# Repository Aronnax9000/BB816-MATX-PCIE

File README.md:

# BB816-PCIe
Adapt Adrien Kohlbecker's BB816 Breakout Board to PCIExpress x16 style connector.

Four slots for expansion cards based on PCIe geometry and the mATX Specification. A 20 pin ATX power supply connector is provided. The board is made to the same specifications as Adrien Kohlbecker's BB816

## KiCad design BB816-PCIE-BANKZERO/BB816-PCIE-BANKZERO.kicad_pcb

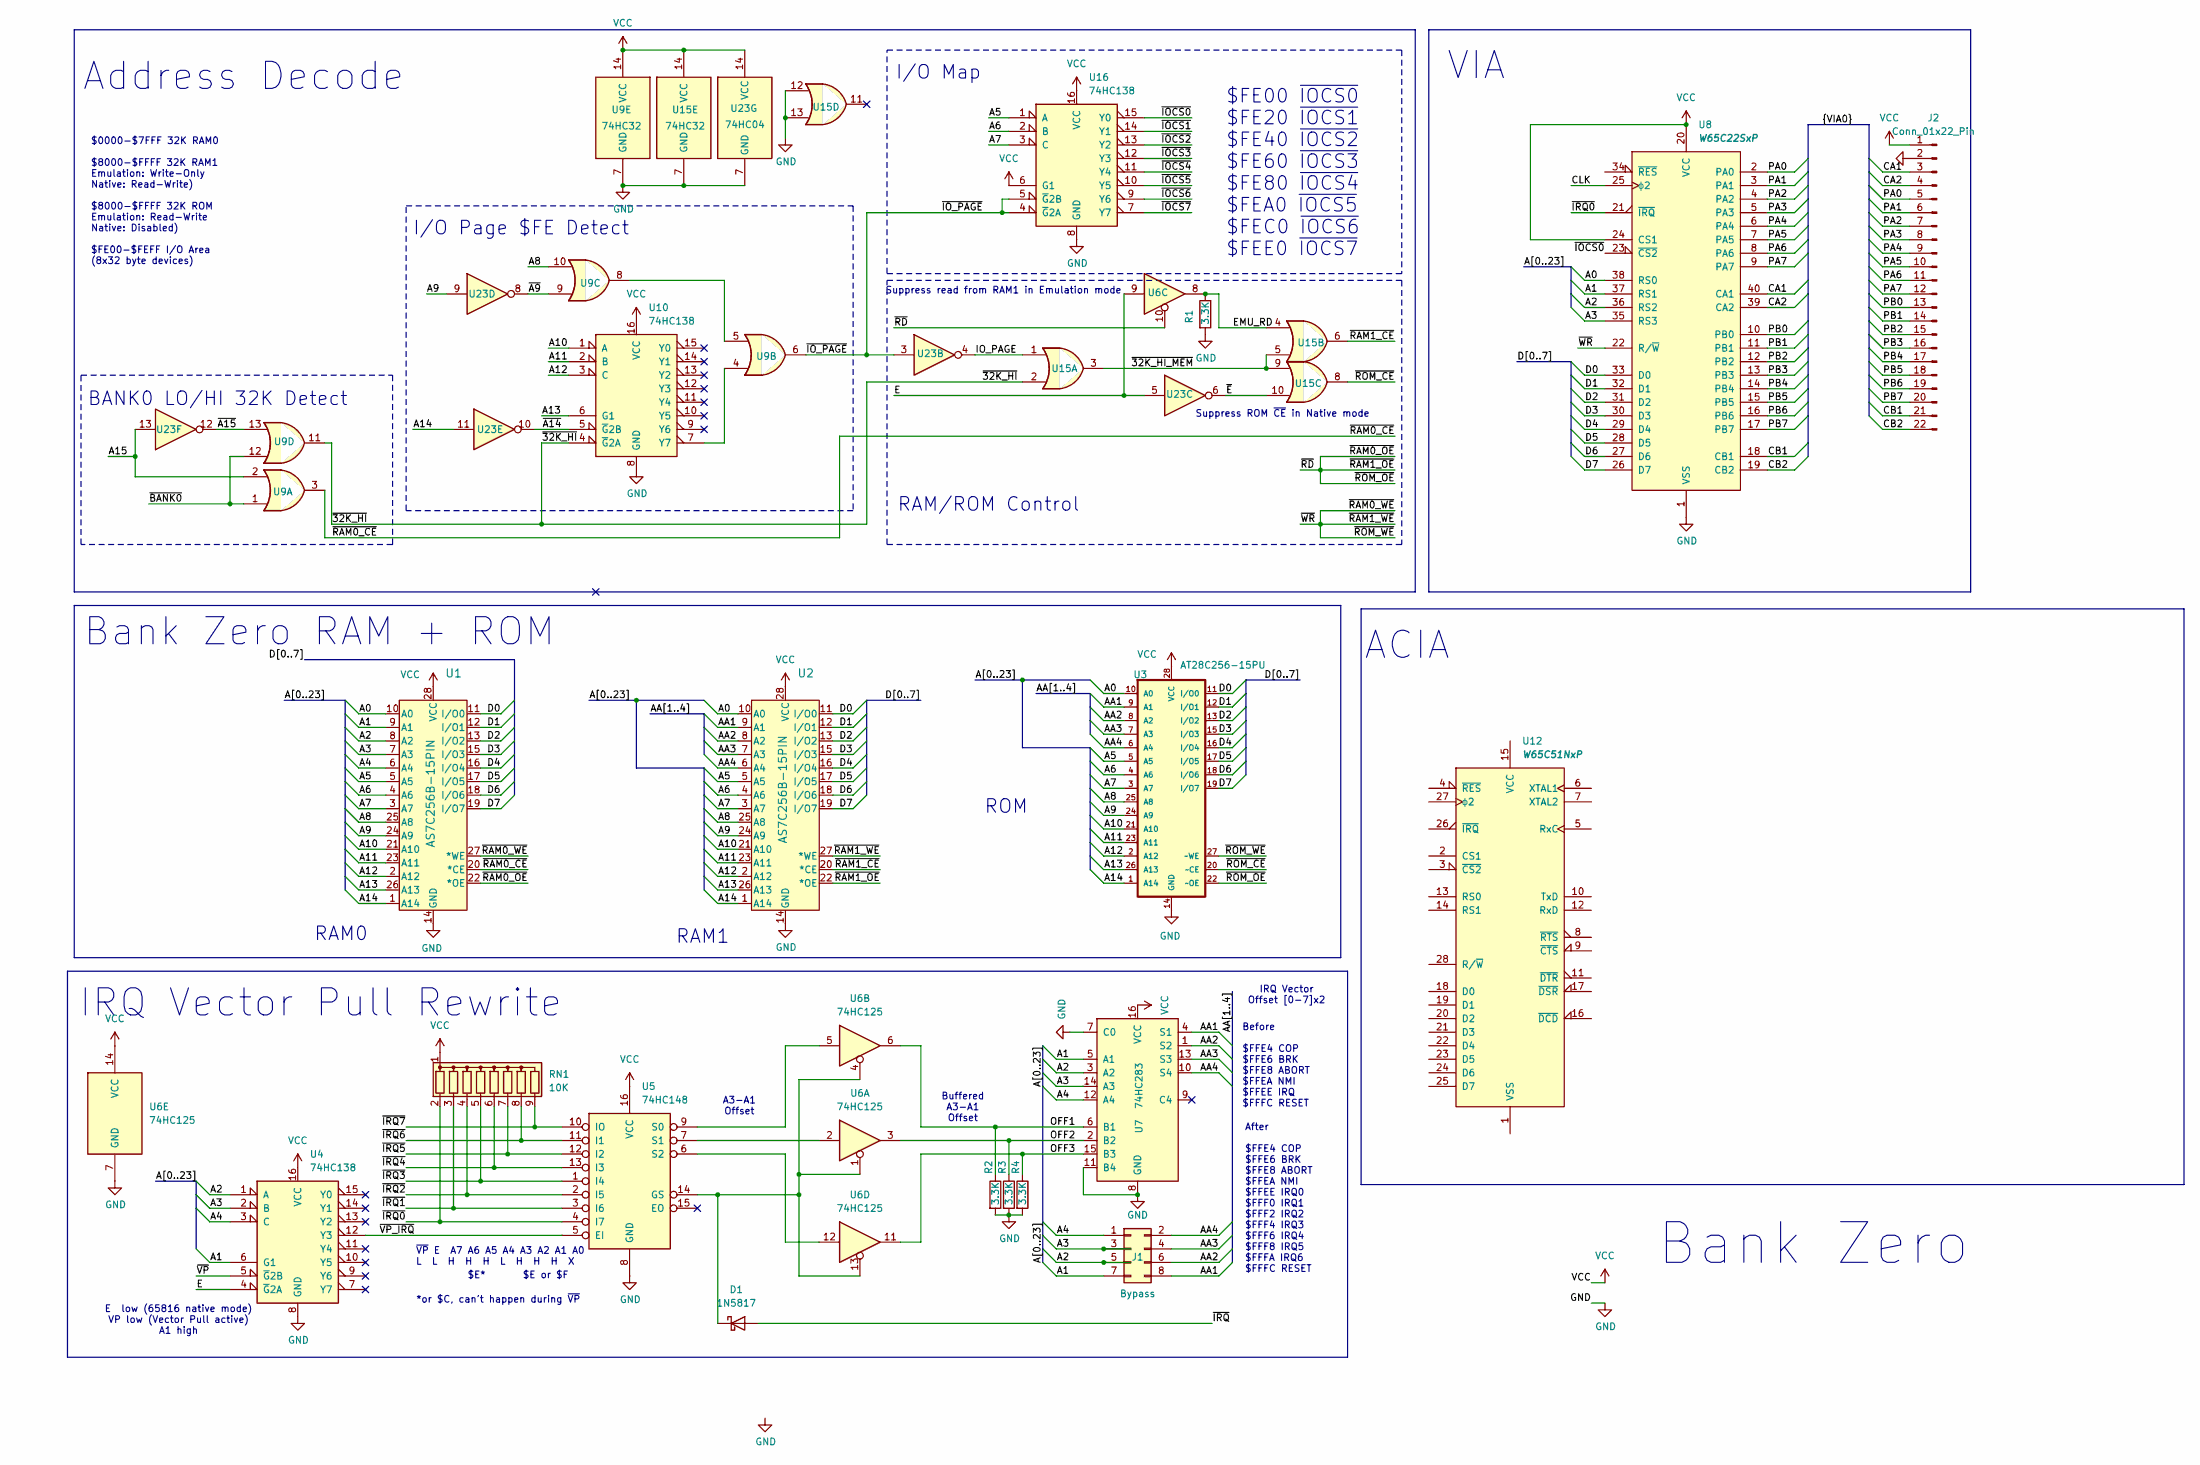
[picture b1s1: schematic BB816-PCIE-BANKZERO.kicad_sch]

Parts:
D1: 1N5817; D_DO-41_SOD81_P10.16mm_Horizontal
J1: Bypass; PinHeader_2x04_P2.54mm_Vertical
J2: Conn_01x22_Pin; PinSocket_1x22_P2.54mm_Horizontal
R1, R2, R3, R4: 3.3K; R_Axial_DIN0207_L6.3mm_D2.5mm_P7.62mm_Horizontal
RN1: 10K; R_Array_SIP9
U1, U2: AS7C256B-15PIN; DIP-28_W7.62mm_Socket
U3: AT28C256-15PU; 228-1277-00-0602J_3MM; MPN AT28C256-15PU
U4, U10, U16: 74HC138; DIP-16_W7.62mm_Socket
U5: 74HC148; DIP-16_W7.62mm_Socket
U6: 74HC125; DIP-14_W7.62mm_Socket
U7: 74HC283; DIP-16_W7.62mm_Socket
U8: W65C22SxP; DIP-40_W15.24mm_Socket
U9, U15: 74HC32; DIP-14_W7.62mm_Socket
U12: W65C51NxP; DIP-28_W15.24mm_Socket
U23: 74HC04; DIP-14_W7.62mm_Socket

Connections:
/A0: U1.10 (A0), U2.10 (A0), U3.10 (A0), U8.38 (RS0)
/A1: J1.7, U1.9 (A1), U4.6 (G1), U7.5 (A1), U8.37 (RS1)
/A2: J1.5, U1.8 (A2), U4.1 (A), U7.3 (A2), U8.36 (RS2)
/A3: J1.3, U1.7 (A3), U4.2 (B), U7.14 (A3), U8.35 (RS3)
/A4: J1.1, U1.6 (A4), U4.3 (C), U7.12 (A4)
/A5: U1.5 (A5), U2.5 (A5), U3.5 (A5), U16.1 (A)
/A6: U1.4 (A6), U2.4 (A6), U3.4 (A6), U16.2 (B)
/A7: U1.3 (A7), U2.3 (A7), U3.3 (A7), U16.3 (C)
/A8: U1.25 (A8), U2.25 (A8), U3.25 (A8), U9.10
/A9: U1.24 (A9), U2.24 (A9), U3.24 (A9), U23.9
/A10: U1.21 (A10), U2.21 (A10), U3.21 (A10), U10.1 (A)
/A11: U1.23 (A11), U2.23 (A11), U3.23 (A11), U10.2 (B)
/A12: U1.2 (A12), U2.2 (A12), U3.2 (A12), U10.3 (C)
/A13: U1.26 (A13), U2.26 (A13), U3.26 (A13), U10.6 (G1)
/A14: U1.1 (A14), U2.1 (A14), U3.1 (A14), U23.11
/A15: U9.2, U23.13
/AA1: J1.8, U2.9 (A1), U3.9 (A1), U7.4 (S1)
/AA2: J1.6, U2.8 (A2), U3.8 (A2), U7.1 (S2)
/AA3: J1.4, U2.7 (A3), U3.7 (A3), U7.13 (S3)
/AA4: J1.2, U2.6 (A4), U3.6 (A4), U7.10 (S4)
/CA1: J2.3, U8.40 (CA1)
/CA2: J2.4, U8.39 (CA2)
/CB1: J2.21, U8.18 (CB1)
/CB2: J2.22, U8.19 (CB2)
/CLK: U8.25 (ϕ2)
/D0: U1.11 (I/O0), U2.11 (I/O0), U3.11 (I/O0), U8.33 (D0)
/D1: U1.12 (I/O1), U2.12 (I/O1), U3.12 (I/O1), U8.32 (D1)
/D2: U1.13 (I/O2), U2.13 (I/O2), U3.13 (I/O2), U8.31 (D2)
/D3: U1.15 (I/O3), U2.15 (I/O3), U3.15 (I/O3), U8.30 (D3)
/D4: U1.16 (I/O4), U2.16 (I/O4), U3.16 (I/O4), U8.29 (D4)
/D5: U1.17 (I/O5), U2.17 (I/O5), U3.17 (I/O5), U8.28 (D5)
/D6: U1.18 (I/O6), U2.18 (I/O6), U3.18 (I/O6), U8.27 (D6)
/D7: U1.19 (I/O7), U2.19 (I/O7), U3.19 (I/O7), U8.26 (D7)
/E: U4.4 (~G2A), U6.9, U23.5
/EMU_RD: R1.1, U6.8, U15.4
/IO_PAGE: U15.1, U23.4
/OFF1: R2.1, U6.6, U7.6 (B1)
/OFF2: R3.1, U6.3, U7.2 (B2)
/OFF3: R4.1, U6.11, U7.15 (B3)
/PA0: J2.5, U8.2 (PA0)
/PA1: J2.6, U8.3 (PA1)
/PA2: J2.7, U8.4 (PA2)
/PA3: J2.8, U8.5 (PA3)
/PA4: J2.9, U8.6 (PA4)
/PA5: J2.10, U8.7 (PA5)
/PA6: J2.11, U8.8 (PA6)
/PA7: J2.12, U8.9 (PA7)
/PB0: J2.13, U8.10 (PB0)
/PB1: J2.14, U8.11 (PB1)
/PB2: J2.15, U8.12 (PB2)
/PB3: J2.16, U8.13 (PB3)
/PB4: J2.17, U8.14 (PB4)
/PB5: J2.18, U8.15 (PB5)
/PB6: J2.19, U8.16 (PB6)
/PB7: J2.20, U8.17 (PB7)
/~32K_HI_MEM: U15.3, U15.5, U15.9
/~32K_HI: U9.11, U10.4 (~G2A), U15.2
/~A9: U9.9, U23.8
/~A14: U10.5 (~G2B), U23.10
/~A15: U9.13, U23.12
/~BANK0: U9.1, U9.12
/~E: U15.10, U23.6
/~IOCS0: U8.23 (~CS2), U16.15 (Y0)
/~IOCS1: U16.14 (Y1)
/~IOCS2: U16.13 (Y2)
/~IOCS3: U16.12 (Y3)
/~IOCS4: U16.11 (Y4)
/~IOCS5: U16.10 (Y5)
/~IOCS6: U16.9 (Y6)
/~IOCS7: U16.7 (Y7)
/~IO_PAGE: U9.6, U16.4 (~G2A), U16.5 (~G2B), U23.3
/~IRQ0: RN1.2 (R1), U5.4 (I7), U8.21 (~IRQ)
/~IRQ1: RN1.3 (R2), U5.3 (I6)
/~IRQ2: RN1.4 (R3), U5.2 (I5)
/~IRQ3: RN1.5 (R4), U5.1 (I4)
/~IRQ4: RN1.6 (R5), U5.13 (I3)
/~IRQ5: RN1.7 (R6), U5.12 (I2)
/~IRQ6: RN1.8 (R7), U5.11 (I1)
/~IRQ7: RN1.9 (R8), U5.10 (IO)
/~IRQ: D1.2 (A)
/~RAM0_CE: U1.20 (*CE), U9.3
/~RAM0_OE: U1.22 (*OE), U2.22 (*OE), U3.22 (~OE), U6.10
/~RAM0_WE: U1.27 (*WE), U2.27 (*WE), U3.27 (~WE), U8.22 (R/~W)
/~RAM1_CE: U2.20 (*CE), U15.6
/~ROM_CE: U3.20 (~CE), U15.8
/~VP_IRQ: U4.12 (Y3), U5.5 (EI)
/~VP: U4.5 (~G2B)
GND: J2.2, R1.2, R2.2, R3.2, R4.2, U1.14 (GND), U2.14 (GND), U3.14 (GND), U4.8 (GND), U5.8 (GND), U6.7 (GND), U7.7 (C0), U7.8 (GND), U7.11 (B4), U8.1 (VSS), U9.7 (GND), U10.8 (GND), U15.7 (GND), U15.12, U15.13, U16.8 (GND), U23.7 (GND)
unnamed: D1.1 (K), U5.14 (GS), U6.1, U6.4, U6.13
unnamed: U5.9 (S0), U6.5
unnamed: U5.7 (S1), U6.2
unnamed: U5.6 (S2), U6.12
unnamed: U9.5, U9.8
unnamed: U9.4, U10.7 (Y7)
VCC: J2.1, RN1.1 (common), U1.28 (VCC), U2.28 (VCC), U3.28 (VCC), U4.16 (VCC), U5.16 (VCC), U6.14 (VCC), U7.16 (VCC), U8.20 (VCC), U8.24 (CS1), U9.14 (VCC), U10.16 (VCC), U15.14 (VCC), U16.6 (G1), U16.16 (VCC), U23.14 (VCC)

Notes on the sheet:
$E or $F
After $FFE4 COP $FFE6 BRK $FFE8 ABORT $FFEA NMI $FFEE IRQ0 $FFF0 IRQ1 $FFF2 IRQ2 $FFF4 IRQ3 $FFF6 IRQ4 $FFF8 IRQ5 $FFFA IRQ6 $FFFC RESET
IRQ Vector Pull Rewrite
ROM
E low (65816 native mode) VP low (Vector Pull active) A1 high
RAM/ROM Control
Buffered A3-A1 Offset
Suppress ROM ~{CE} in Native mode
Before $FFE4 COP $FFE6 BRK $FFE8 ABORT $FFEA NMI $FFEE IRQ $FFFC RESET
BANK0 LO/HI 32K Detect
ACIA
Address Decode
Bank Zero RAM + ROM
$E*
~{VP} E A7 A6 A5 A4 A3 A2 A1 A0 L L H H H L H H H X
VIA
$FE00 ~{IOCS0} $FE20 ~{IOCS1} $FE40 ~{IOCS2} $FE60 ~{IOCS3} $FE80 ~{IOCS4} $FEA0 ~{IOCS5} $FEC0 ~{IOCS6} $FEE0 ~{IOCS7}
Suppress read from RAM1 in Emulation mode
RAM1
Bank Zero
A3-A1 Offset
I/O Map
I/O Page $FE Detect
*or $C, can't happen during ~{VP}
$0000-$7FFF 32K RAM0 $8000-$FFFF 32K RAM1 Emulation: Write-Only Native: Read-Write) $8000-$FFFF 32K ROM Emulation: Read-Write Native: Disabled) $FE00-$FEFF I/O Area (8x32 byte devices)
RAM0
IRQ Vector Offset [0-7]x2

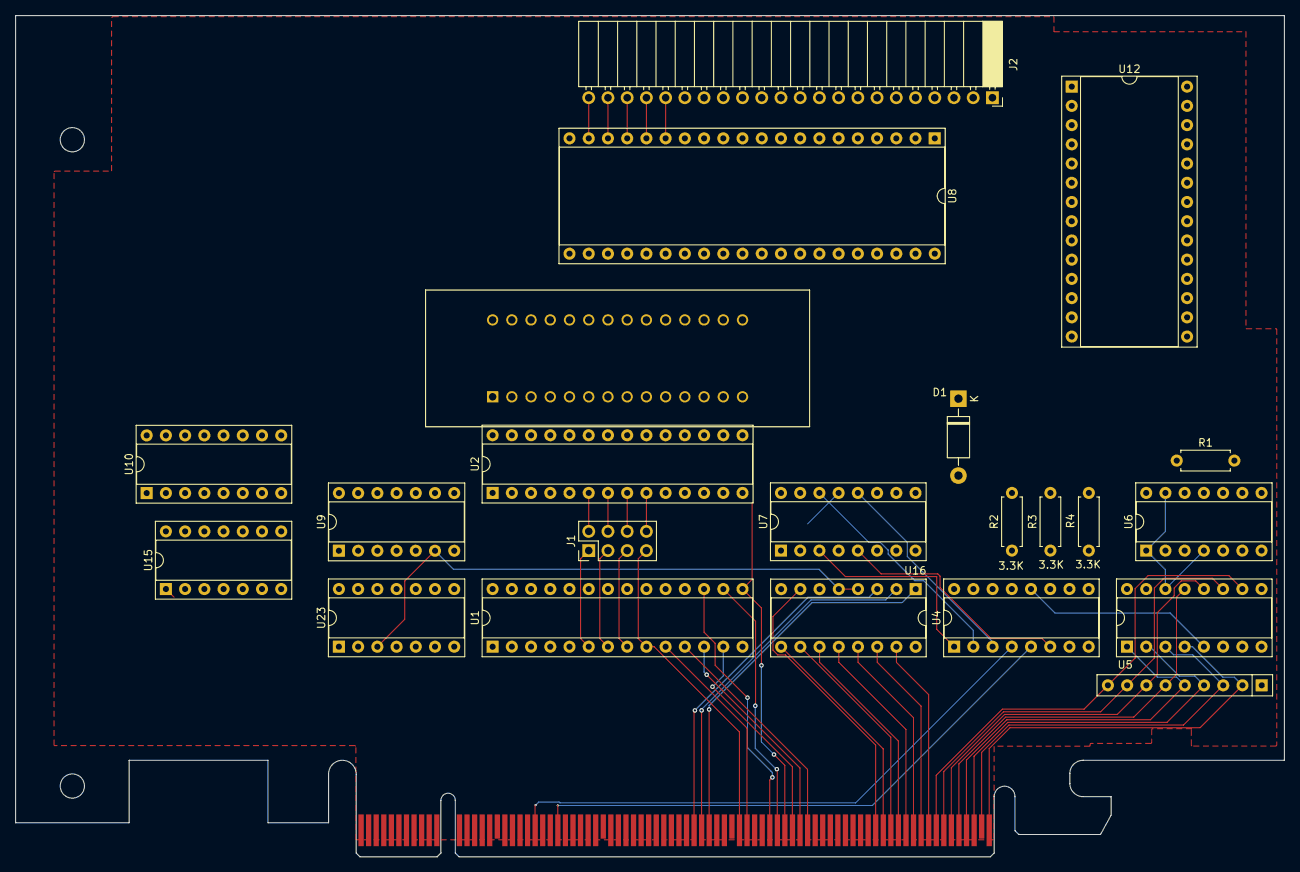
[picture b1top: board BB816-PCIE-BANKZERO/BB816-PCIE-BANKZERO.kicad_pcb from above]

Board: 4 copper layers, 167.7 x 111.1 mm, 22 parts (0 on the bottom side), 85 nets.

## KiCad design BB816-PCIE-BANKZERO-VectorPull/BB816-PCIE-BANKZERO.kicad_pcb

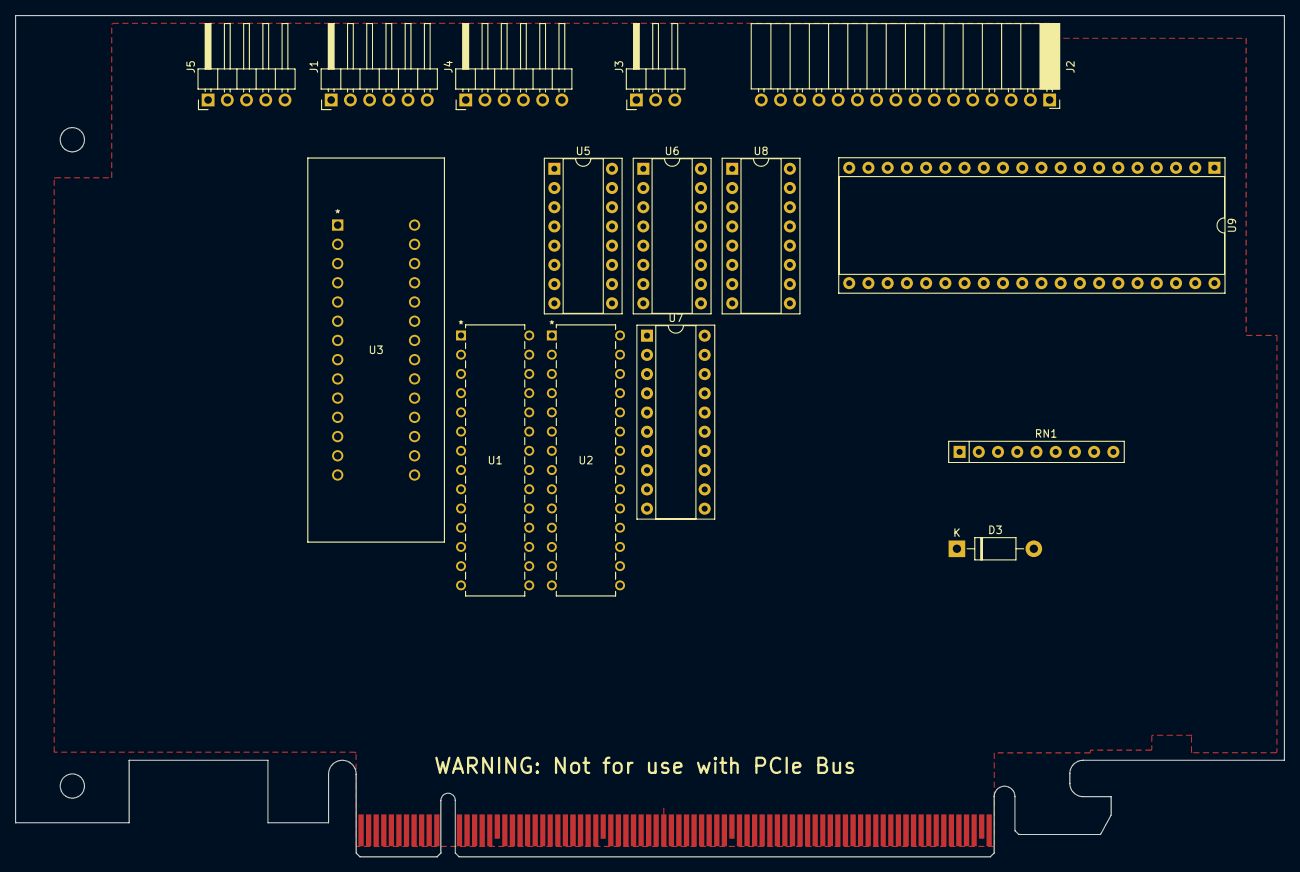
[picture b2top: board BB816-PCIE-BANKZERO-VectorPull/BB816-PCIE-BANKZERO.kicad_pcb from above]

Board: 4 copper layers, 167.6 x 111.2 mm, 16 parts (0 on the bottom side), 58 nets.

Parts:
D3: 1N5817; D_DO-41_SOD81_P10.16mm_Horizontal
J1: SPI_0; PinHeader_1x06_P2.54mm_Horizontal
J1#2: BB816_BreakoutA27_PCIex16; PCIexpress_x16_HW_FH
J2: LCD Display; PinSocket_1x16_P2.54mm_Horizontal
J3: LCD Backlight; PinHeader_1x03_P2.54mm_Horizontal
J4: SPI_1; PinHeader_1x06_P2.54mm_Horizontal
J5: GPIO; PinHeader_1x05_P2.54mm_Horizontal
RN1: 10K; R_Array_SIP9
U1, U2: AS7C256B-15PIN; PDIP-28_MIL300_ALL
U3: AT28C256-15PU; 228-1277-00-0602J_3MM
U5: 74HC138; DIP-16_W7.62mm_Socket
U6: 74HC148; DIP-16_W7.62mm_Socket
U7: 74HC244; DIP-20_W7.62mm_Socket
U8: 74HC283; DIP-16_W7.62mm_Socket
U9: W65C22SxP; DIP-40_W15.24mm_Socket

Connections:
/A0: J1#2.B50 (A0), U1.10 (A0), U2.10 (A0), U3.10 (A0), U9.38 (RS0)
/A1: J1#2.B49 (A1), U1.9 (A1), U5.6 (G1), U8.5 (A1), U9.37 (RS1)
/A2: J1#2.B48 (A2), U1.8 (A2), U5.1 (A), U8.3 (A2), U9.36 (RS2)
/A3: J1#2.B47 (A3), U1.7 (A3), U5.2 (B), U8.14 (A3), U9.35 (RS3)
/A4: J1#2.B46 (A4), U1.6 (A4), U5.3 (C), U8.12 (A4)
/A5: J1#2.B45 (A5), U1.5 (A5), U2.5 (A5), U3.5 (A5)
/A6: J1#2.B44 (A6), U1.4 (A6), U2.4 (A6), U3.4 (A6)
/A7: J1#2.B43 (A7), U1.3 (A7), U2.3 (A7), U3.3 (A7)
/A8: J1#2.B42 (A8), U1.25 (A8), U2.25 (A8), U3.25 (A8)
/A9: J1#2.B41 (A9), U1.24 (A9), U2.24 (A9), U3.24 (A9)
/A10: J1#2.B40 (A10), U1.21 (A10), U2.21 (A10), U3.21 (A10)
/A11: J1#2.B39 (A11), U1.23 (A11), U2.23 (A11), U3.23 (A11)
/A12: J1#2.B38 (A12), U1.2 (A12), U2.2 (A12), U3.2 (A12)
/A13: J1#2.B37 (A13), U1.26 (A13), U2.26 (A13), U3.26 (A13)
/A14: J1#2.B36 (A14), U1.1 (A14), U2.1 (A14), U3.1 (A14)
/AA1: U2.9 (A1), U3.9 (A1), U8.4 (S1)
/AA2: U2.8 (A2), U3.8 (A2), U8.1 (S2)
/AA3: U2.7 (A3), U3.7 (A3), U8.13 (S3)
/AA4: U2.6 (A4), U3.6 (A4), U8.10 (S4)
/CLK: J1#2.B8 (CLK), U9.25 (ϕ2)
/D0: J1#2.B58 (D0), U1.11 (I/O0), U2.11 (I/O0), U3.19 (I/O7), U9.33 (D0)
/D1: J1#2.B57 (D1), U1.12 (I/O1), U2.12 (I/O1), U3.18 (I/O6), U9.32 (D1)
/D2: J1#2.B56 (D2), U1.13 (I/O2), U2.13 (I/O2), U3.17 (I/O5), U9.31 (D2)
/D3: J1#2.B55 (D3), U1.15 (I/O3), U2.15 (I/O3), U3.16 (I/O4), U9.30 (D3)
/D4: J1#2.B54 (D4), U1.16 (I/O4), U2.16 (I/O4), U3.15 (I/O3), U9.29 (D4)
/D5: J1#2.B53 (D5), U1.17 (I/O5), U2.17 (I/O5), U3.13 (I/O2), U9.28 (D5)
/D6: J1#2.B52 (D6), U1.18 (I/O6), U2.18 (I/O6), U3.12 (I/O1), U9.27 (D6)
/D7: J1#2.B51 (D7), U1.19 (I/O7), U2.19 (I/O7), U3.11 (I/O0), U9.26 (D7)
/E: J1#2.B22 (E), U5.5 (~G2B)
/PB0: J1.3 (~CS), J2.11 (D4), U9.10 (PB0)
/PB1: J2.12 (D5), J4.3 (~CS), U9.11 (PB1)
/PB2: J1.4 (SCK), J2.13 (D6), J4.4 (SCK), U9.12 (PB2)
/PB3: J1.5 (SDI), J2.14 (D7), J4.5 (SDI), U9.13 (PB3)
/PB4: J1.6 (SDO), J2.4 (RS), J4.6 (SDO), U9.14 (PB4)
/PB5: J2.5 (R~W), J5.3, U9.15 (PB5)
/PB6: J2.6 (E), J5.4, U9.16 (PB6)
/PB7: J5.5, U9.17 (PB7)
/~IRQ0: J1#2.B82 (X82), RN1.2 (R1), U6.4 (I7)
/~IRQ1: J1#2.B81 (X81), RN1.3 (R2), U6.3 (I6)
/~IRQ2: J1#2.B80 (X80), RN1.4 (R3), U6.2 (I5)
/~IRQ3: J1#2.B79 (X79), RN1.5 (R4), U6.1 (I4)
/~IRQ4: J1#2.B78 (X78), RN1.6 (R5), U6.13 (I3)
/~IRQ5: J1#2.B77 (X77), RN1.7 (R6), U6.12 (I2)
/~IRQ6: J1#2.B76 (X76), RN1.8 (R7), U6.11 (I1)
/~IRQ7: J1#2.B75 (X75), RN1.9 (R8), U6.10 (IO)
/~IRQ: D3.2 (A), J1#2.B10 (~IRQ)
/~VP: J1#2.B25 (~VP), U5.4 (~G2A)
GND: J1.2 (GND), J1#2.A1 (GND), J1#2.A2 (GND), J1#2.A3 (GND), J1#2.A4 (GND), J1#2.A5 (GND), J1#2.A6 (GND), J1#2.A7 (GND), J1#2.A8 (GND), J1#2.A9 (GND), J1#2.A10 (GND), J1#2.A11 (GND), J1#2.A12 (GND), J1#2.A13 (GND), J1#2.A14 (GND), J1#2.A15 (GND), J1#2.A16 (GND), J1#2.A17 (GND), J1#2.A18 (GND), J1#2.A19 (GND), J1#2.A20 (GND), J1#2.A21 (GND), J1#2.A22 (GND), J1#2.A23 (GND), J1#2.A24 (GND), J1#2.A25 (GND), J1#2.A26 (GND), J1#2.A27 (GND), J1#2.A28 (GND), J1#2.A29 (GND), J1#2.A30 (GND), J1#2.A31 (GND), J1#2.A32 (GND), J1#2.A33 (GND), J1#2.A34 (GND), J1#2.A35 (GND), J1#2.A36 (GND), J1#2.A37 (GND), J1#2.A38 (GND), J1#2.A39 (GND), J1#2.A40 (GND), J1#2.A41 (GND), J1#2.A42 (GND), J1#2.A43 (GND), J1#2.A44 (GND), J1#2.A45 (GND), J1#2.A46 (GND), J1#2.A47 (GND), J1#2.A48 (GND), J1#2.A49 (GND), J1#2.A50 (GND), J1#2.A51 (GND), J1#2.A52 (GND), J1#2.A53 (GND), J1#2.A54 (GND), J1#2.A55 (GND), J1#2.A56 (GND), J1#2.A57 (GND), J1#2.A58 (GND), J1#2.A59 (GND), J1#2.A60 (GND), J1#2.A61 (GND), J1#2.A62 (GND), J1#2.A63 (GND), J1#2.A64 (GND), J1#2.A65 (GND), J1#2.A66 (GND), J1#2.A67 (GND), J1#2.A68 (GND), J1#2.A69 (GND), J1#2.A70 (GND), J1#2.A71 (GND), J1#2.A72 (GND), J1#2.A73 (GND), J1#2.A74 (GND), J1#2.A75 (GND), J1#2.A76 (GND), J1#2.A77 (GND), J1#2.A78 (GND), J1#2.A79 (GND), J1#2.A80 (GND), J1#2.A81 (GND), J1#2.A82 (GND), J1#2.B2 (GND), J2.1 (VSS), J2.16 (K), J3.3 (K), J4.2 (GND), J5.2, U1.14 (GND), U2.14 (GND), U3.14 (GND), U5.8 (GND), U6.8 (GND), U7.10 (GND), U8.7 (C0), U8.8 (GND), U8.11 (B4), U9.1 (VSS)
unnamed: D3.1 (K), U6.14 (GS)
unnamed: J2.3 (V0), J3.2 (V0)
unnamed: U5.12 (Y3), U6.5 (EI)
unnamed: U6.9 (S0), U7.15 (2A1)
unnamed: U6.7 (S1), U7.13 (2A2)
unnamed: U6.6 (S2), U7.11 (2A3)
unnamed: U7.5 (2Y1), U8.6 (B1)
unnamed: U7.7 (2Y2), U8.2 (B2)
unnamed: U7.9 (2Y3), U8.15 (B3)
VCC: J1.1 (VCC), J1#2.B1 (VCC), J2.2 (VDD), J2.15 (A), J3.1 (A), J4.1 (VCC), J5.1, U1.28 (VCC), U2.28 (VCC), U3.28 (VCC), U5.16 (VCC), U6.16 (VCC), U7.1 (1OE), U7.2 (1A0), U7.4 (1A1), U7.6 (1A2), U7.8 (1A3), U7.17 (2A0), U7.20 (VCC), U8.16 (VCC), U9.20 (VCC)

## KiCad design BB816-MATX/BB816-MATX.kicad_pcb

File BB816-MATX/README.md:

# BB816-MATX

A mATX (Micro-ATX) form factor system board for Adrien Kohlbecker's [BB816](https://github.com/adrienkohlbecker/BB816) Breakout Board, rev. A27.

This project adapts an [ATX layout](https://github.com/theguydanish/CM4_MATX) created by Oliver Møller for the (archived) CM4_MATX project.

In addition to the breakout board connector, the system board provides four bus connectors of the type used for PCIExpress x16 add-on cards, and an ATX power supply connector.

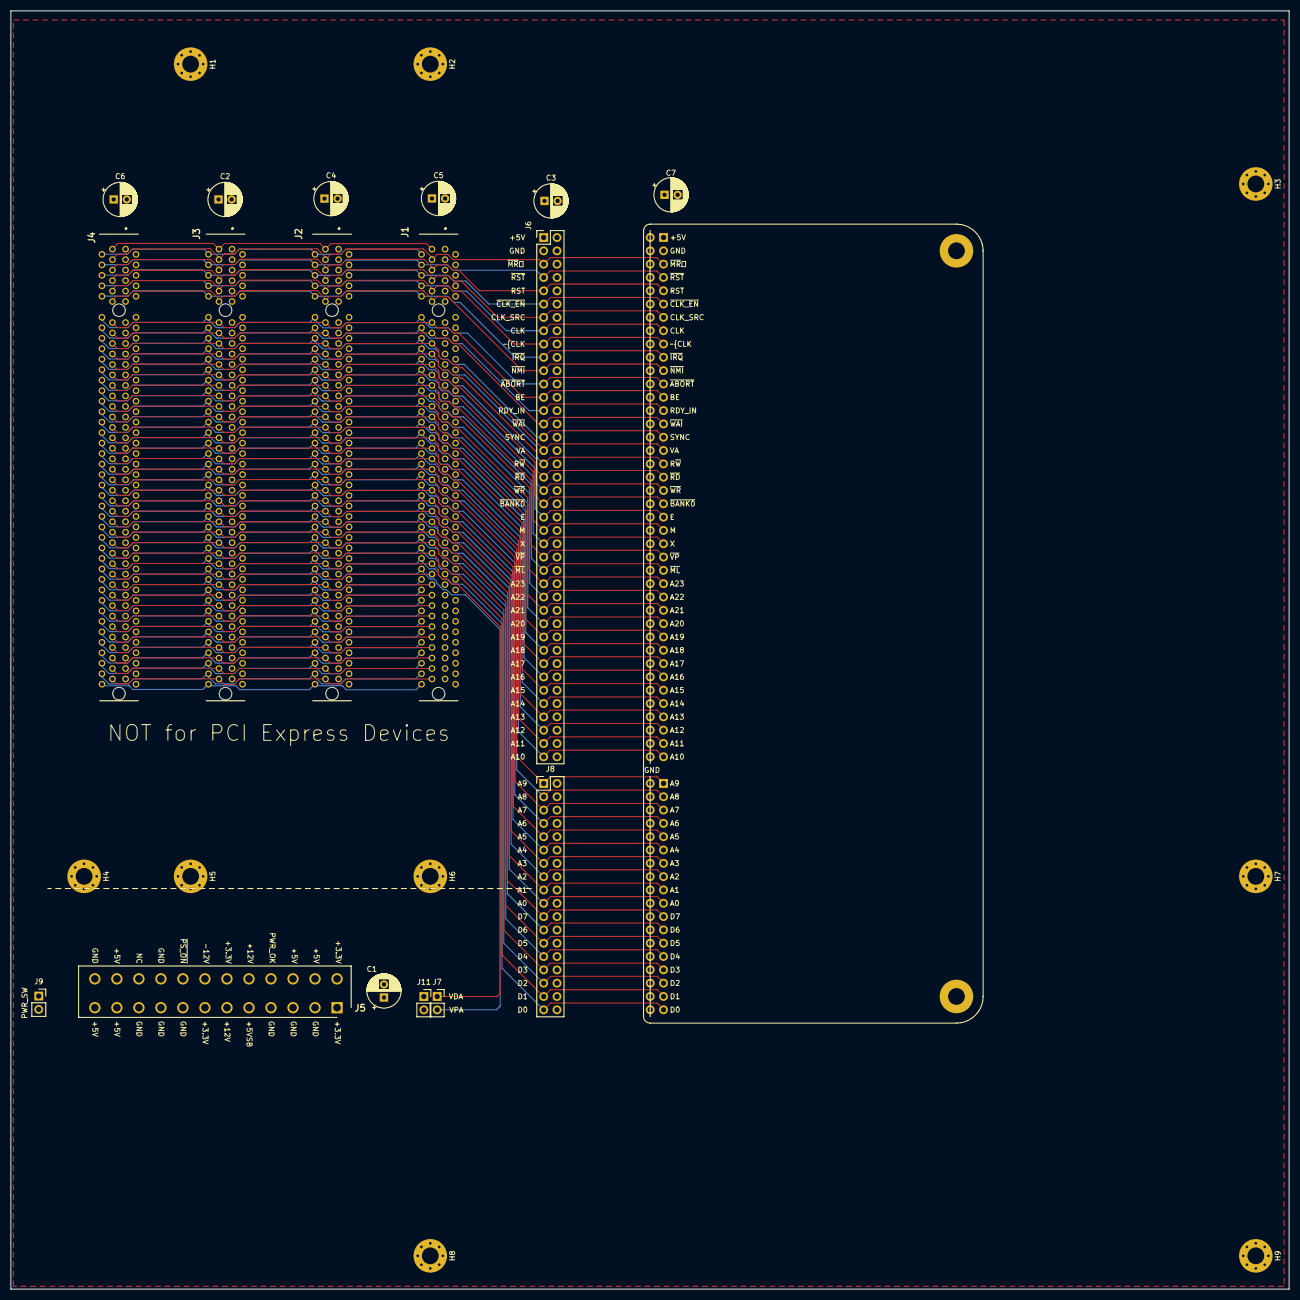
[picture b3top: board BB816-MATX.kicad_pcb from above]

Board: 4 copper layers, 243.8 x 243.8 mm, 27 parts (0 on the bottom side), 85 nets.

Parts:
C1, C2, C3, C4, C5, C6, C7: 220u; CP_Radial_D6.3mm_P2.50mm
H1, H2, H3, H4, H5, H6, H7, H8, H9: MountingHole; MountingHole_3.2mm_M3_Pad_Via
J1, J2, J3, J4: 10018783-10113TLF
J5: 39-28-1243; SHDR24W125P550X420_2X12_5160X960X1310P
J6: PinSocket_2x40_P2.54mm_Vertical_Flip
J7, J11: PinSocket_1x02_P2.54mm_Vertical
J8: PinSocket_2x18_P2.54mm_Vertical_Flip
J9: PWR_SW; PinSocket_1x02_P2.54mm_Vertical
J10: BB816_Breakout_A27; BB816_Breakout_A27_Socket_NO_VDPA

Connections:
/+3.3v: J5.2 (+3.3v), J5.12 (+3.3v), J5.13 (+3.3v)
/+12v: J5.10 (+12v), J5.11 (+12v)
/A0: J1.B50, J2.B50, J3.B50, J4.B50, J8.19, J10.b50 (A0)
/A1: J1.B49, J2.B49, J3.B49, J4.B49, J8.17, J10.b49 (A1)
/A2: J1.B48, J2.B48, J3.B48, J4.B48, J8.15, J10.b48 (A2)
/A3: J1.B47, J2.B47, J3.B47, J4.B47, J8.13, J10.b47 (A3)
/A4: J1.B46, J2.B46, J3.B46, J4.B46, J8.11, J10.b46 (A4)
/A5: J1.B45, J2.B45, J3.B45, J4.B45, J8.9, J10.b45 (A5)
/A6: J1.B44, J2.B44, J3.B44, J4.B44, J8.7, J10.b44 (A6)
/A7: J1.B43, J2.B43, J3.B43, J4.B43, J8.5, J10.b43 (A7)
/A8: J1.B42, J2.B42, J3.B42, J4.B42, J8.3, J10.b42 (A8)
/A9: J1.B41, J2.B41, J3.B41, J4.B41, J8.1, J10.b41 (A9)
/A10: J1.B40, J2.B40, J3.B40, J4.B40, J6.79, J10.b40 (A10)
/A11: J1.B39, J2.B39, J3.B39, J4.B39, J6.77, J10.b39 (A11)
/A12: J1.B38, J2.B38, J3.B38, J4.B38, J6.75, J10.b38 (A12)
/A13: J1.B37, J2.B37, J3.B37, J4.B37, J6.73, J10.b37 (A13)
/A14: J1.B36, J2.B36, J3.B36, J4.B36, J6.71, J10.b36 (A14)
/A15: J1.B35, J2.B35, J3.B35, J4.B35, J6.69, J10.b35 (A15)
/A16: J1.B34, J2.B34, J3.B34, J4.B34, J6.67, J10.b34 (A16)
/A17: J1.B33, J2.B33, J3.B33, J4.B33, J6.65, J10.b33 (A17)
/A18: J1.B32, J2.B32, J3.B32, J4.B32, J6.63, J10.b32 (A18)
/A19: J1.B31, J2.B31, J3.B31, J4.B31, J6.61, J10.b31 (A19)
/A20: J1.B30, J2.B30, J3.B30, J4.B30, J6.59, J10.b30 (A20)
/A21: J1.B29, J2.B29, J3.B29, J4.B29, J6.57, J10.b29 (A21)
/A22: J1.B28, J2.B28, J3.B28, J4.B28, J6.55, J10.b28 (A22)
/A23: J1.B27, J2.B27, J3.B27, J4.B27, J6.53, J10.b27 (A23)
/BE: J1.B13, J2.B13, J3.B13, J4.B13, J6.25, J10.b13 (BE)
/CLK: J1.B8, J2.B8, J3.B8, J4.B8, J6.15, J10.b8 (CLK)
/CLK_SRC: J1.B7, J2.B7, J3.B7, J4.B7, J6.13, J10.b7 (CLK_SRC)
/D0: J1.B58, J2.B58, J3.B58, J4.B58, J8.35, J10.b58 (D0)
/D1: J1.B57, J2.B57, J3.B57, J4.B57, J8.33, J10.b57 (D1)
/D2: J1.B56, J2.B56, J3.B56, J4.B56, J8.31, J10.b56 (D2)
/D3: J1.B55, J2.B55, J3.B55, J4.B55, J8.29, J10.b55 (D3)
/D4: J1.B54, J2.B54, J3.B54, J4.B54, J8.27, J10.b54 (D4)
/D5: J1.B53, J2.B53, J3.B53, J4.B53, J8.25, J10.b53 (D5)
/D6: J1.B52, J2.B52, J3.B52, J4.B52, J8.23, J10.b52 (D6)
/D7: J1.B51, J2.B51, J3.B51, J4.B51, J8.21, J10.b51 (D7)
/E: J1.B22, J2.B22, J3.B22, J4.B22, J6.43, J10.b22 (E)
/M: J1.B23, J2.B23, J3.B23, J4.B23, J6.45, J10.b23 (M)
/PS_ON: J5.16 (PS_ON#), J9.1
/RDY_IN: J1.B14, J2.B14, J3.B14, J4.B14, J6.27, J10.b14 (RDY_IN)
/RST: J1.B5, J2.B5, J3.B5, J4.B5, J6.9, J10.b5 (RST)
/R~W: J1.B18, J2.B18, J3.B18, J4.B18, J6.35, J10.b18 (R~W)
/SYNC: J1.B16, J2.B16, J3.B16, J4.B16, J6.31, J10.b16 (SYNC)
/VA: J1.B17, J2.B17, J3.B17, J4.B17, J6.33, J10.b17 (VA)
/VDA: J1.B59, J2.B59, J3.B59, J4.B59, J7.1, J11.1
/VPA: J1.B60, J2.B60, J3.B60, J4.B60, J7.2, J11.2
/X: J1.B24, J2.B24, J3.B24, J4.B24, J6.47, J10.b24 (X)
/X61: J1.B61, J2.B61, J3.B61, J4.B61
/X62: J1.B62, J2.B62, J3.B62, J4.B62
/X63: J1.B63, J2.B63, J3.B63, J4.B63
/X64: J1.B64, J2.B64, J3.B64, J4.B64
/X65: J1.B65, J2.B65, J3.B65, J4.B65
/X66: J1.B66, J2.B66, J3.B66, J4.B66
/~ABORT: J1.B12, J2.B12, J3.B12, J4.B12, J6.23, J10.b12 (~ABORT)
/~BANK0: J1.B21, J2.B21, J3.B21, J4.B21, J6.41, J10.b21 (~BANK0)
/~CLK_EN: J1.B6, J2.B6, J3.B6, J4.B6, J6.11, J10.b6 (~CLK_EN)
/~CLK: J1.B9, J2.B9, J3.B9, J4.B9, J6.17, J10.b9 (~CLK)
/~IOCS0: J1.B74, J2.B74, J3.B74, J4.B74
/~IOCS1: J1.B73, J2.B73, J3.B73, J4.B73
/~IOCS2: J1.B72, J2.B72, J3.B72, J4.B72
/~IOCS3: J1.B71, J2.B71, J3.B71, J4.B71
/~IOCS4: J1.B70, J2.B70, J3.B70, J4.B70
/~IOCS5: J1.B69, J2.B69, J3.B69, J4.B69
/~IOCS6: J1.B68, J2.B68, J3.B68, J4.B68
/~IOCS7: J1.B67, J2.B67, J3.B67, J4.B67
/~IRQ0: J1.B82, J2.B82, J3.B82, J4.B82
/~IRQ1: J1.B81, J2.B81, J3.B81, J4.B81
/~IRQ2: J1.B80, J2.B80, J3.B80, J4.B80
/~IRQ3: J1.B79, J2.B79, J3.B79, J4.B79
/~IRQ4: J1.B78, J2.B78, J3.B78, J4.B78
/~IRQ5: J1.B77, J2.B77, J3.B77, J4.B77
/~IRQ6: J1.B76, J2.B76, J3.B76, J4.B76
/~IRQ7: J1.B75, J2.B75, J3.B75, J4.B75
/~IRQ: J1.B10, J2.B10, J3.B10, J4.B10, J6.19, J10.b10 (~IRQ)
/~ML: J1.B26, J2.B26, J3.B26, J4.B26, J6.51, J10.b26 (~ML)
/~MR⎒: J1.B3, J2.B3, J3.B3, J4.B3, J6.5, J10.b3 (~MR⎒)
/~NMI: J1.B11, J2.B11, J3.B11, J4.B11, J6.21, J10.b11 (~NMI)
/~RD: J1.B19, J2.B19, J3.B19, J4.B19, J6.37, J10.b19 (~RD)
/~RST: J1.B4, J2.B4, J3.B4, J4.B4, J6.7, J10.b4 (~RST)
/~VP: J1.B25, J2.B25, J3.B25, J4.B25, J6.49, J10.b25 (~VP)
/~WAI: J1.B15, J2.B15, J3.B15, J4.B15, J6.29, J10.b15 (~WAI)
/~WR: J1.B20, J2.B20, J3.B20, J4.B20, J6.39, J10.b20 (~WR)
GND: C1.2, C2.2, C3.2, C4.2, C5.2, C6.2, C7.2, J1.A1, J1.A2, J1.A3, J1.A4, J1.A5, J1.A6, J1.A7, J1.A8, J1.A9, J1.A10, J1.A11, J1.A12, J1.A13, J1.A14, J1.A15, J1.A16, J1.A17, J1.A18, J1.A19, J1.A20, J1.A21, J1.A22, J1.A23, J1.A24, J1.A25, J1.A26, J1.A27, J1.A28, J1.A29, J1.A30, J1.A31, J1.A32, J1.A33, J1.A34, J1.A35, J1.A36, J1.A37, J1.A38, J1.A39, J1.A40, J1.A41, J1.A42, J1.A43, J1.A44, J1.A45, J1.A46, J1.A47, J1.A48, J1.A49, J1.A50, J1.A51, J1.A52, J1.A53, J1.A54, J1.A55, J1.A56, J1.A57, J1.A58, J1.A59, J1.A60, J1.A61, J1.A62, J1.A63, J1.A64, J1.A65, J1.A66, J1.A67, J1.A68, J1.A69, J1.A70, J1.A71, J1.A72, J1.A73, J1.A74, J1.A75, J1.A76, J1.A77, J1.A78, J1.A79, J1.A80, J1.A81, J1.A82, J1.B2, J2.A1, J2.A2, J2.A3, J2.A4, J2.A5, J2.A6, J2.A7, J2.A8, J2.A9, J2.A10, J2.A11, J2.A12, J2.A13, J2.A14, J2.A15, J2.A16, J2.A17, J2.A18, J2.A19, J2.A20, J2.A21, J2.A22, J2.A23, J2.A24, J2.A25, J2.A26, J2.A27, J2.A28, J2.A29, J2.A30, J2.A31, J2.A32, J2.A33, J2.A34, J2.A35, J2.A36, J2.A37, J2.A38, J2.A39, J2.A40, J2.A41, J2.A42, J2.A43, J2.A44, J2.A45, J2.A46, J2.A47, J2.A48, J2.A49, J2.A50, J2.A51, J2.A52, J2.A53, J2.A54, J2.A55, J2.A56, J2.A57, J2.A58, J2.A59, J2.A60, J2.A61, J2.A62, J2.A63, J2.A64, J2.A65, J2.A66, J2.A67, J2.A68, J2.A69, J2.A70, J2.A71, J2.A72, J2.A73, J2.A74, J2.A75, J2.A76, J2.A77, J2.A78, J2.A79, J2.A80, J2.A81, J2.A82, J2.B2, J3.A1, J3.A2, J3.A3, J3.A4, J3.A5, J3.A6, J3.A7, J3.A8, J3.A9, J3.A10, J3.A11, J3.A12, J3.A13, J3.A14, J3.A15, J3.A16, J3.A17, J3.A18, J3.A19, J3.A20, J3.A21, J3.A22, J3.A23, J3.A24, J3.A25, J3.A26, J3.A27, J3.A28, J3.A29, J3.A30, J3.A31, J3.A32, J3.A33, J3.A34, J3.A35, J3.A36, J3.A37, J3.A38, J3.A39, J3.A40, J3.A41, J3.A42, J3.A43, J3.A44, J3.A45, J3.A46, J3.A47, J3.A48, J3.A49, J3.A50, J3.A51, J3.A52, J3.A53, J3.A54, J3.A55, J3.A56, J3.A57, J3.A58, J3.A59, J3.A60, J3.A61, J3.A62, J3.A63, J3.A64, J3.A65, J3.A66, J3.A67, J3.A68, J3.A69, J3.A70, J3.A71, J3.A72, J3.A73, J3.A74, J3.A75, J3.A76, J3.A77, J3.A78, J3.A79, J3.A80, J3.A81, J3.A82, J3.B2, J4.A1, J4.A2, J4.A3, J4.A4, J4.A5, J4.A6, J4.A7, J4.A8, J4.A9, J4.A10, J4.A11, J4.A12, J4.A13, J4.A14, J4.A15, J4.A16, J4.A17, J4.A18, J4.A19, J4.A20, J4.A21, J4.A22, J4.A23, J4.A24, J4.A25, J4.A26, J4.A27, J4.A28, J4.A29, J4.A30, J4.A31, J4.A32, J4.A33, J4.A34, J4.A35, J4.A36, J4.A37, J4.A38, J4.A39, J4.A40, J4.A41, J4.A42, J4.A43, J4.A44, J4.A45, J4.A46, J4.A47, J4.A48, J4.A49, J4.A50, J4.A51, J4.A52, J4.A53, J4.A54, J4.A55, J4.A56, J4.A57, J4.A58, J4.A59, J4.A60, J4.A61, J4.A62, J4.A63, J4.A64, J4.A65, J4.A66, J4.A67, J4.A68, J4.A69, J4.A70, J4.A71, J4.A72, J4.A73, J4.A74, J4.A75, J4.A76, J4.A77, J4.A78, J4.A79, J4.A80, J4.A81, J4.A82, J4.B2, J5.3 (GND), J5.5 (GND), J5.7 (GND), J5.15 (GND), J5.17 (GND), J5.18 (GND), J5.19 (GND), J5.24 (GND), J6.2, J6.3, J6.4, J6.6, J6.8, J6.10, J6.12, J6.14, J6.16, J6.18, J6.20, J6.22, J6.24, J6.26, J6.28, J6.30, J6.32, J6.34, J6.36, J6.38, J6.40, J6.42, J6.44, J6.46, J6.48, J6.50, J6.52, J6.54, J6.56, J6.58, J6.60, J6.62, J6.64, J6.66, J6.68, J6.70, J6.72, J6.74, J6.76, J6.78, J6.80, J8.2, J8.4, J8.6, J8.8, J8.10, J8.12, J8.14, J8.16, J8.18, J8.20, J8.22, J8.24, J8.26, J8.28, J8.30, J8.32, J8.34, J8.36, J9.2, J10.a2 (GND), J10.a3 (GND), J10.a4 (GND), J10.a5 (GND), J10.a6 (GND), J10.a7 (GND), J10.a8 (GND), J10.a9 (GND), J10.a10 (GND), J10.a11 (GND), J10.a12 (GND), J10.a13 (GND), J10.a14 (GND), J10.a15 (GND), J10.a16 (GND), J10.a17 (GND), J10.a18 (GND), J10.a19 (GND), J10.a20 (GND), J10.a21 (GND), J10.a22 (GND), J10.a23 (GND), J10.a24 (GND), J10.a25 (GND), J10.a26 (GND), J10.a27 (GND), J10.a28 (GND), J10.a29 (GND), J10.a30 (GND), J10.a31 (GND), J10.a32 (GND), J10.a33 (GND), J10.a34 (GND), J10.a35 (GND), J10.a36 (GND), J10.a37 (GND), J10.a38 (GND), J10.a39 (GND), J10.a40 (GND), J10.a41 (GND), J10.a42 (GND), J10.a43 (GND), J10.a44 (GND), J10.a45 (GND), J10.a46 (GND), J10.a47 (GND), J10.a48 (GND), J10.a49 (GND), J10.a50 (GND), J10.a51 (GND), J10.a52 (GND), J10.a53 (GND), J10.a54 (GND), J10.a55 (GND), J10.a56 (GND), J10.a57 (GND), J10.a58 (GND), J10.b2 (GND)
VCC: C1.1, C2.1, C3.1, C4.1, C5.1, C6.1, C7.1, J1.B1, J2.B1, J3.B1, J4.B1, J5.4 (+5v), J5.6 (+5v), J5.21 (+5v), J5.22 (+5v), J5.23 (+5v), J6.1, J10.b1 (VCC)

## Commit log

2024-02-25 Create test
2024-02-29 BankZero
2024-03-06 big commit
2024-03-06 Bum AND
2024-03-06 Cleanup
2024-03-06 Bad PCB
2024-03-07 Add VIA and ACIA
2024-03-08 Stuff
